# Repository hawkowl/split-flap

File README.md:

# Split-Flap

This repository contains:

- `PCB/Unit`, comprising of the PCB for the per-module controller
- `Unit/`, comprising of the firmware for the individual module controller
- `Controller/`, comprising of the firmware for a RP2040 controller for multiple modules

## Sources

- Original Design: [Split Flap Display by David Kingsman](https://www.printables.com/model/69464-split-flap-display).
- Flaps: [OpenSCAD flaps by rtitmuss](https://github.com/rtitmuss/splitflap/tree/main/OpenSCAD)
- Frame: [Modification by rtitmuss](https://www.printables.com/model/518882-split-flap-frame)

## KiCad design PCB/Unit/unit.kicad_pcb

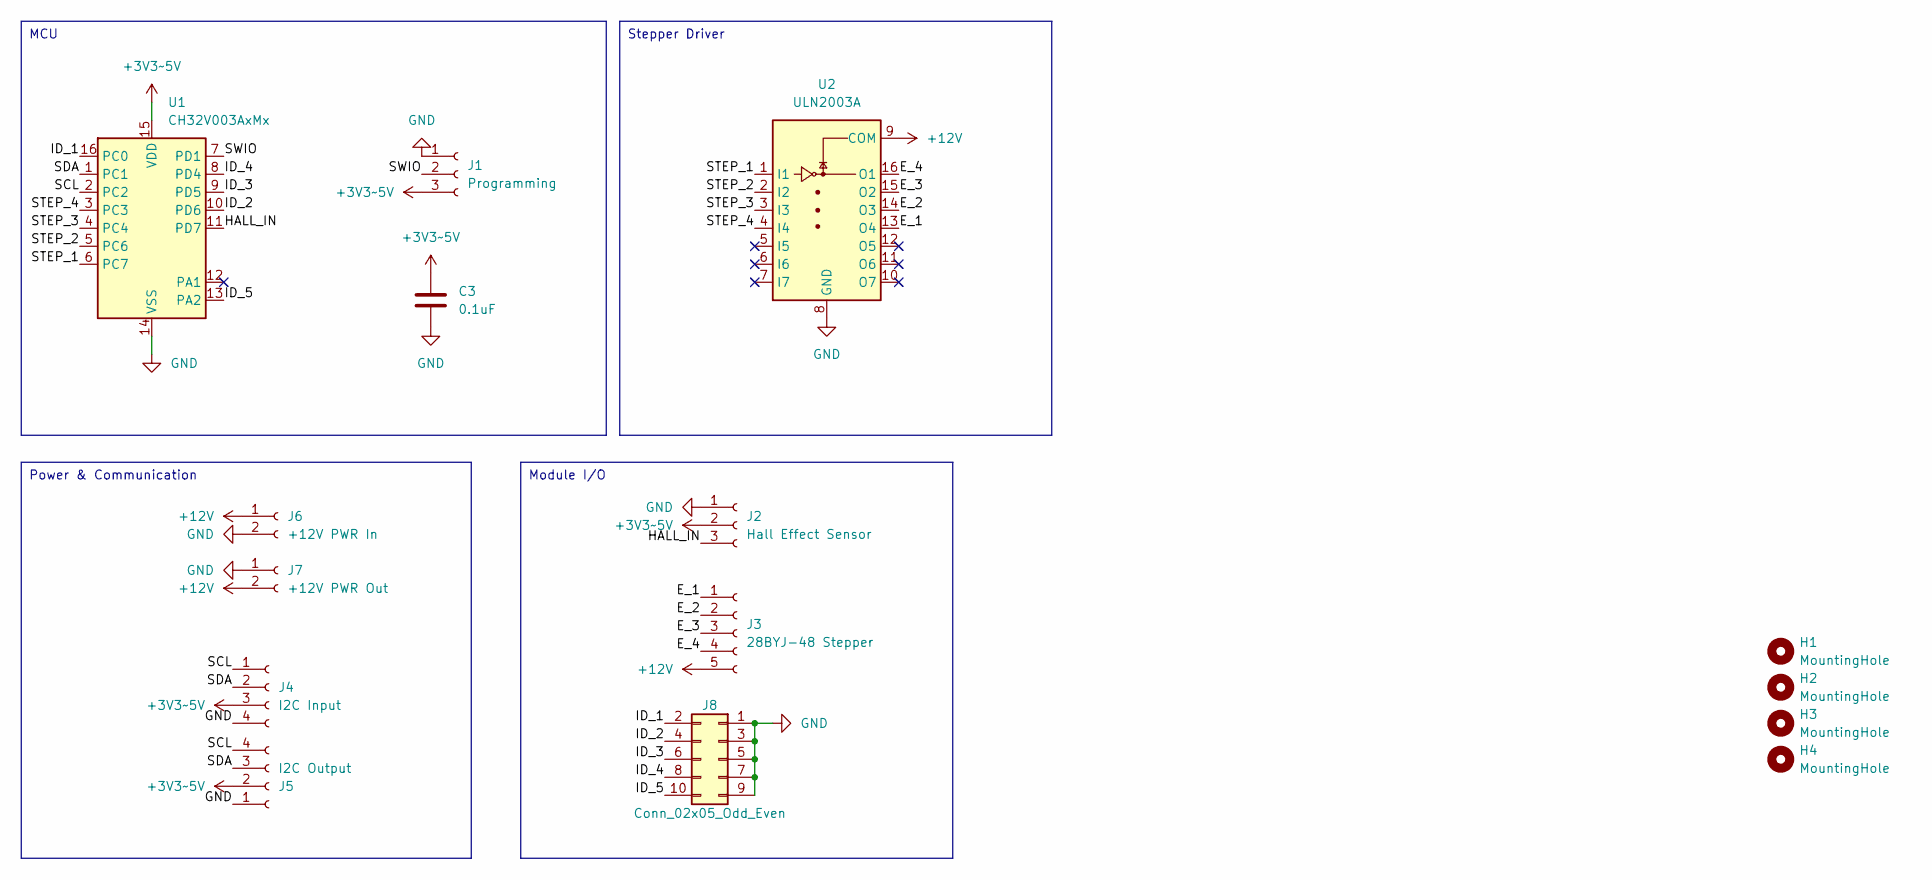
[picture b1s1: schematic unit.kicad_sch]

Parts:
C3: 0.1uF; C_1206_3216Metric_Symbol
H1, H2, H3, H4: MountingHole; MountingHole_3.2mm_M3
J1: Programming; JST_XH_B3B-XH-A_1x03_P2.50mm_Vertical
J2: Hall Effect Sensor; JST_XH_B3B-XH-A_1x03_P2.50mm_Vertical
J3: 28BYJ-48 Stepper; JST_XH_B5B-XH-A_1x05_P2.50mm_Vertical_LABELLED
J4: I2C Input; JST_XH_B4B-XH-A_1x04_P2.50mm_Vertical_LABELLED
J5: I2C Output; JST_XH_B4B-XH-A_1x04_P2.50mm_Vertical_LABELLED
J6: +12V PWR In; JST_XH_B2B-XH-A_1x02_P2.50mm_Vertical_LABELLED
J7: +12V PWR Out; JST_XH_B2B-XH-A_1x02_P2.50mm_Vertical_LABELLED
J8: Conn_02x05_Odd_Even; PinSocket_2x05_P2.54mm_Vertical
U1: CH32V003AxMx; SOP-16_3.9x9.9mm_P1.27mm
U2: ULN2003A; SOP-16_3.9x9.9mm_P1.27mm

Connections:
+3V3~5V: C3.2, J1.3, J2.2, J4.3, J5.2, U1.15 (VDD)
+12V: J3.5, J6.1, J7.2, U2.9 (COM)
/E_1: J3.1, U2.13 (O4)
/E_2: J3.2, U2.14 (O3)
/E_3: J3.3, U2.15 (O2)
/E_4: J3.4, U2.16 (O1)
/HALL_IN: J2.3, U1.11 (PD7)
/ID_1: J8.2, U1.16 (PC0)
/ID_2: J8.4, U1.10 (PD6)
/ID_3: J8.6, U1.9 (PD5)
/ID_4: J8.8, U1.8 (PD4)
/ID_5: J8.10, U1.13 (PA2)
/SCL: J4.1, J5.4, U1.2 (PC2)
/SDA: J4.2, J5.3, U1.1 (PC1)
/STEP_1: U1.6 (PC7), U2.1 (I1)
/STEP_2: U1.5 (PC6), U2.2 (I2)
/STEP_3: U1.4 (PC4), U2.3 (I3)
/STEP_4: U1.3 (PC3), U2.4 (I4)
/SWIO: J1.2, U1.7 (PD1)
GND: C3.1, J1.1, J2.1, J4.4, J5.1, J6.2, J7.1, J8.1, J8.3, J8.5, J8.7, J8.9, U1.14 (VSS), U2.8 (GND)

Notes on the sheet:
Module I/O
MCU
Power & Communication
Stepper Driver

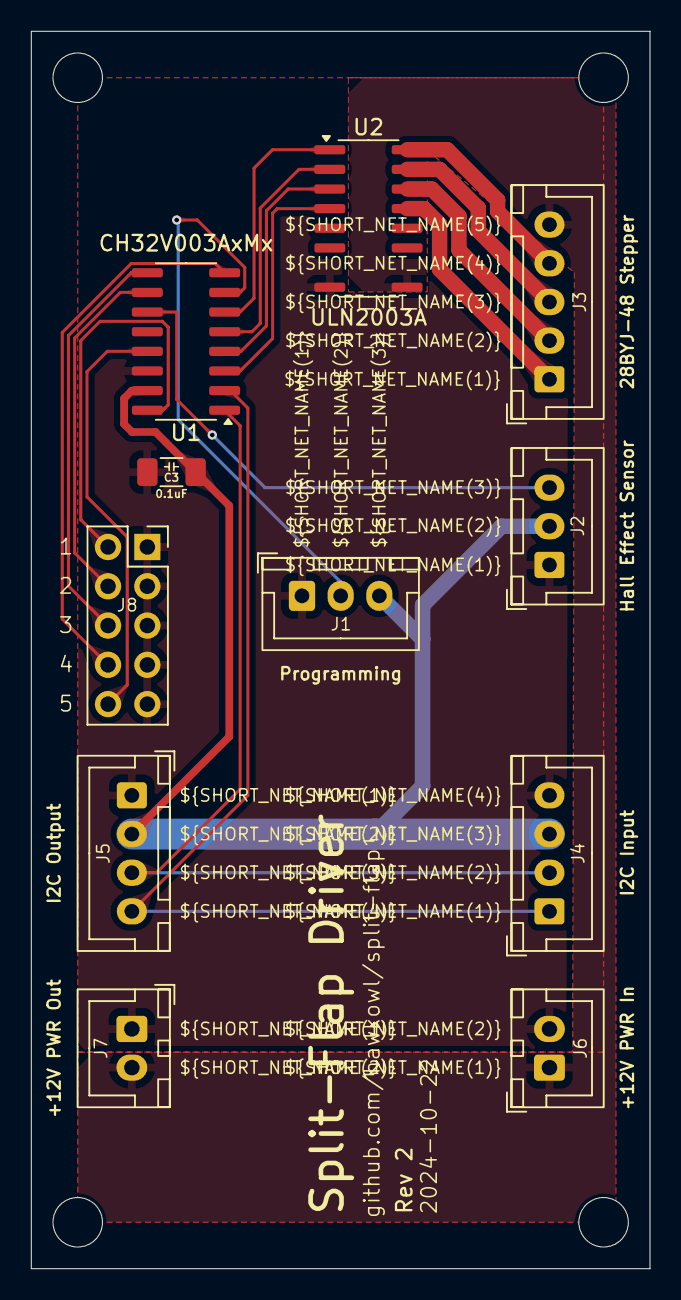
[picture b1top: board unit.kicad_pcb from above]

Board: 2 copper layers, 40.0 x 80.0 mm, 15 parts (0 on the bottom side), 20 nets.

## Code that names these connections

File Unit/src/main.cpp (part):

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#define SERIAL_ENABLE  // uncomment for serial debug communication

// Pins of I2C address switch
#define ADRESSSW4 PC0
#define ADRESSSW3 PD6
#define ADRESSSW2 PD5
#define ADRESSSW1 PD4

// constants stepper
#define STEPPERPIN1 PC6
#define STEPPERPIN2 PC7
#define STEPPERPIN3 PC3
#define STEPPERPIN4 PC4
#define HALLPIN PD7

#define STEPS 2038  // 28BYJ-48 stepper, number of steps
#define AMOUNTFLAPS 45
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  printf("I2CAddress: %d\n", i2cAddress);
#endif

  funPinMode(PC1, GPIO_CFGLR_OUT_10Mhz_AF_OD);  // SDA
  funPinMode(PC2, GPIO_CFGLR_OUT_10Mhz_AF_OD);  // SCL

  SetupI2CSlave(i2cAddress, i2c_registers, sizeof(i2c_registers), receiveLetter,
                requestEvent, false);
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
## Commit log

2024-09-26 init
2024-11-25 add safestring dep
2024-11-25 Add license file
2024-11-25 update after pycon au
2024-11-25 PCB+schematic
2024-11-25 readme
